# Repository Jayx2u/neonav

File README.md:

# neonav
neonav is a three degrees of freedom mouse designed for intuitive navigation in 3D virtual environments. Traditional 2D mice fall short when you need to move fluidly through three-dimensional spaces - especially when you're modeling in CAD software. This input device captures motion across three axes (X, Y, and Z), allowing you to push, pull, tilt, and rotate your way through 3D environments with natural hand movements.

## PCB

## Case

## PCB Schematic

## Bill of Materials
| Value             | Quantity | Unit Price (USD) | Ext. Price (USD) | LCSC Link                                                                                                                                                   |
|-------------------|----------|------------------|------------------|-------------------------------------------------------------------------------------------------------------------------------------------------------------|
| 0805X5R106K500NT  | 1        | 0.0709           | 0.71             | https://lcsc.com/product-detail/Multilayer-Ceramic-Capacitors-MLCC-SMD-SMT_AIDE-CAPACITOR-0805X5R106K500NT_C48579582.html?s_z=n_10uF%25200805%2520capacitor |
| WS2812B           | 4        | 0.0924           | 0.46             | https://lcsc.com/product-detail/RGB-LEDs-Built-in-IC_Worldsemi-WS2812B-V5-W_C2874885.html?s_z=n_WS2812B                                                     |
| ARG05FTC5000      | 1        | 0.0087           | 0.44             | https://lcsc.com/product-detail/Chip-Resistor-Surface-Mount_Viking-ARG05FTC5000_C2828857.html?s_z=n_500%2520ohm%25200805%2520resisto                        |
| XIAO-RP2040-SMD   | 1        |                  | 4.28             | https://www.aliexpress.com/item/1005003682505451.html                                                                                                       |
| TLV493DA1B6HTSA2  | 1        | 0.9012           | 0.90             | https://lcsc.com/product-detail/3D-Magnetic-Sensors_Infineon-TLV493DA1B6HTSA2_C126688.html?s_z=n_TLV493DA1B6HTSA2                                           |
|                   |          |                  |                  |                                                                                                                                                             |
| LCSC Shipping     |          | 24.07            |                  |                                                                                                                                                             |
| LCSC Handling Fee |          | 3                |                  |                                                                                                                                                             |
| JLCPCB PCB        |          | 2.00             |                  |                                                                                                                                                             |
| JLCPCB Shipping   |          | 11.01            |                  |                                                                                                                                                             |
|                   |          |                  |                  |                                                                                                                                                             |
**Total: $42.59**

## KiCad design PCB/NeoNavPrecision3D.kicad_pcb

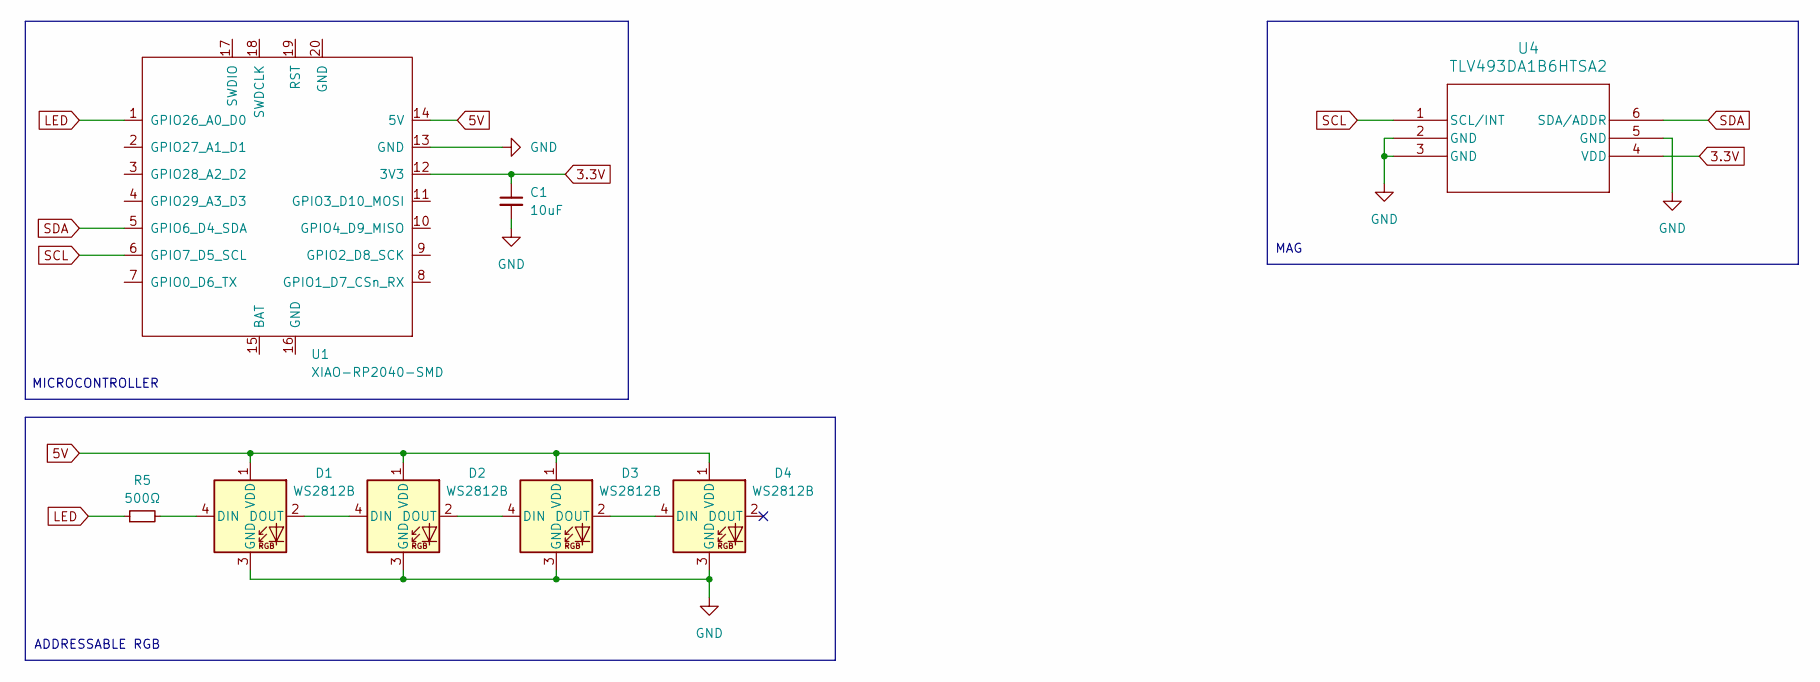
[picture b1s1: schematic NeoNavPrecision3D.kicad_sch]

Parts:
C1: 10uF; C_0805_2012Metric_Pad1.18x1.45mm_HandSolder
D1, D2, D3, D4: WS2812B; LED_WS2812B_PLCC4_5.0x5.0mm_P3.2mm
R5: 500Ω; D_0805_2012Metric_Pad1.15x1.40mm_HandSolder
U1: XIAO-RP2040-SMD
U4: TLV493DA1B6HTSA2; PG-TSOP6-6-5_INF

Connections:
3.3V: C1.1, U1.12 (3V3), U4.4 (VDD)
5V: D1.1 (VDD), D2.1 (VDD), D3.1 (VDD), D4.1 (VDD), U1.14 (5V)
GND: C1.2, D1.3 (GND), D2.3 (GND), D3.3 (GND), D4.3 (GND), U1.13 (GND), U4.2 (GND), U4.3 (GND), U4.5 (GND)
LED: R5.1, U1.1 (GPIO26_A0_D0)
unnamed: D1.4 (DIN), R5.2
unnamed: D1.2 (DOUT), D2.4 (DIN)
unnamed: D2.2 (DOUT), D3.4 (DIN)
unnamed: D3.2 (DOUT), D4.4 (DIN)
SCL: U1.6 (GPIO7_D5_SCL), U4.1 (SCL/INT)
SDA: U1.5 (GPIO6_D4_SDA), U4.6 (SDA/ADDR)

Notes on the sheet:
ADDRESSABLE RGB
MAG
MICROCONTROLLER

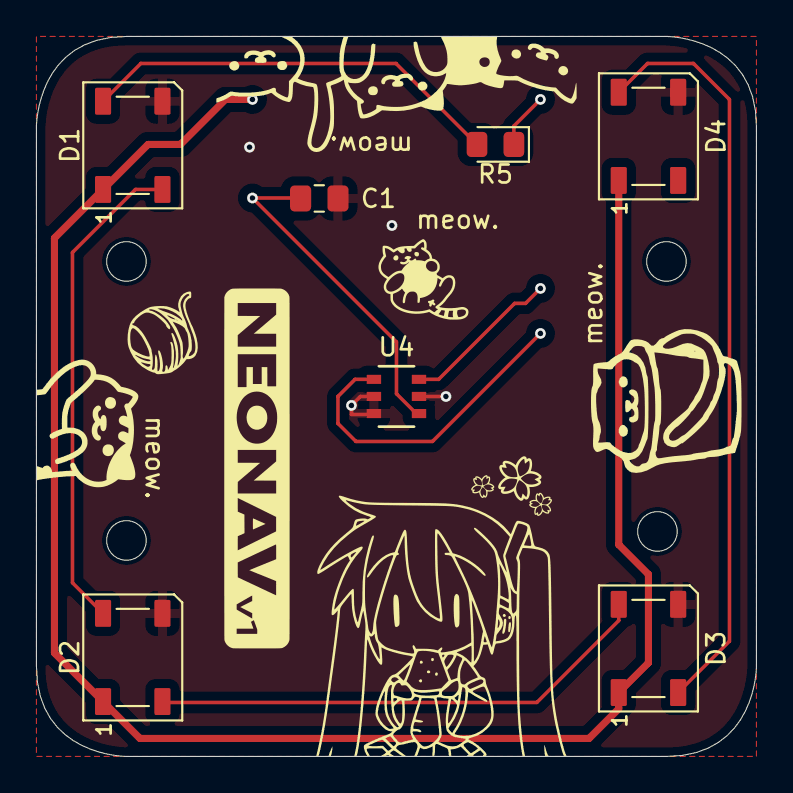
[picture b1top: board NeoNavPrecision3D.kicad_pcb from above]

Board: 2 copper layers, 40.0 x 40.0 mm, 8 parts (1 on the bottom side), 10 nets.

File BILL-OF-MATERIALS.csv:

Value,Quantity,LCSC Link
0805X5R106K500NT,1,https://lcsc.com/product-detail/Multilayer-Ceramic-Capacitor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
WS2812B,4,https://lcsc.com/product-detail/RGB-LEDs-Built-in-IC_Worldse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
ARG05FTC5000,1,https://lcsc.com/product-detail/Chip-Resistor-Surface-Mount_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
XIAO-RP2040-SMD,1,https://www.aliexpress.com/item/1005003682505451.html
TLV493DA1B6HTSA2,1,https://lcsc.com/product-detail/3D-Magnetic-Sensors_Infineon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

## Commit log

2025-06-12 Add "final final this one for real" PCB revision
2025-06-25 Update Journal and add assets
2025-06-25 Update Journal and assets
2025-07-09 Update JOURNAL
2025-07-31 Add KiCAD project and production files
2025-07-31 Update pcb files
2025-08-01 Update journal entry
2025-08-01 Add CAD files
2025-08-01 Add BOM and showcase files
2025-08-01 Add total hours spent
2025-08-01 Update BOM with costs
